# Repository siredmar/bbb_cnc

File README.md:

bbb_cnc
=======

Beaglebone Black Cape for CNC machines

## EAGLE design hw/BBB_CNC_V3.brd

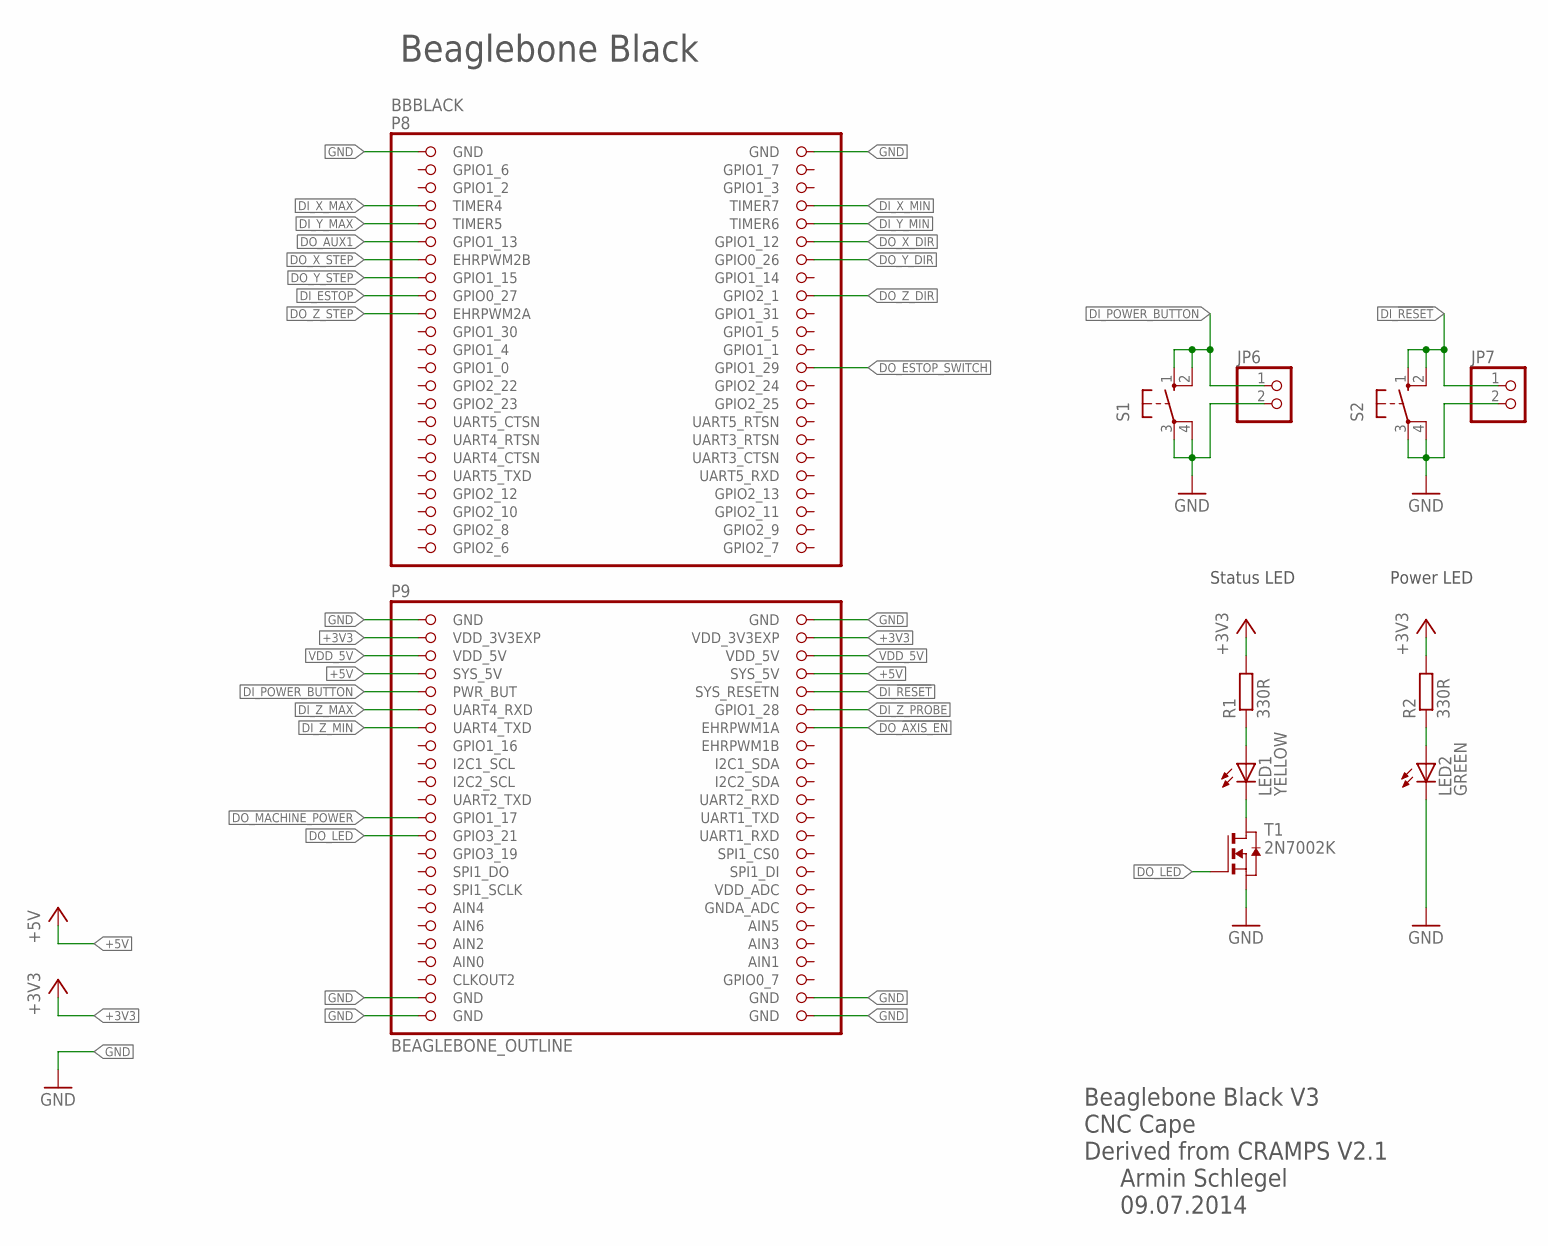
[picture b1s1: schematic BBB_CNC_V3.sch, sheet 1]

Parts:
BBBLACK: BEAGLEBONE_OUTLINE; BEAGLEBONE_SHIELD
JP6, JP7: PINHD-1X2; 1X02
LED1: YELLOW; SML0805
LED2: GREEN; SML0805
R1, R2: 330R; R0603
S1, S2: 10-XX; B3F-10XX
T1: 2N7002K; SOT-23

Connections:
+3V3: BBBLACK.49 (VDD_3V3EXP), BBBLACK.50 (VDD_3V3EXP), R1.2, R2.2; also elsewhere on the board
+5V: BBBLACK.53 (SYS_5V), BBBLACK.54 (SYS_5V); also elsewhere on the board
AIN0: BBBLACK.85 (AIN0)
DI_!RESET: BBBLACK.56 (SYS_RESETN), JP7.1, S2.1 (S), S2.2 (S1)
DI_ESTOP: BBBLACK.17 (GPIO0_27); also elsewhere on the board
DI_POWER_BUTTON: BBBLACK.55 (PWR_BUT), JP6.1, S1.1 (S), S1.2 (S1)
DI_X_MAX: BBBLACK.7 (TIMER4); also elsewhere on the board
DI_X_MIN: BBBLACK.8 (TIMER7); also elsewhere on the board
DI_Y_MAX: BBBLACK.9 (TIMER5); also elsewhere on the board
DI_Y_MIN: BBBLACK.10 (TIMER6); also elsewhere on the board
DI_Z_MAX: BBBLACK.57 (UART4_RXD); also elsewhere on the board
DI_Z_MIN: BBBLACK.59 (UART4_TXD); also elsewhere on the board
DI_Z_PROBE: BBBLACK.58 (GPIO1_28); also elsewhere on the board
DO_!AXIS_EN: BBBLACK.60 (EHRPWM1A); also elsewhere on the board
DO_AUX1: BBBLACK.11 (GPIO1_13); also elsewhere on the board
DO_ESTOP_SWITCH: BBBLACK.26 (GPIO1_29); also elsewhere on the board
DO_LED: BBBLACK.71 (GPIO3_21), T1.3 (G)
DO_MACHINE_POWER: BBBLACK.69 (GPIO1_17); also elsewhere on the board
DO_X_DIR: BBBLACK.12 (GPIO1_12); also elsewhere on the board
DO_X_STEP: BBBLACK.13 (EHRPWM2B); also elsewhere on the board
DO_Y_DIR: BBBLACK.14 (GPIO0_26); also elsewhere on the board
DO_Y_STEP: BBBLACK.15 (GPIO1_15); also elsewhere on the board
DO_Z_DIR: BBBLACK.18 (GPIO2_1); also elsewhere on the board
DO_Z_STEP: BBBLACK.19 (EHRPWM2A); also elsewhere on the board
GND: BBBLACK.1 (GND), BBBLACK.2 (GND), BBBLACK.47 (GND), BBBLACK.48 (GND), BBBLACK.89 (GND), BBBLACK.90 (GND), BBBLACK.91 (GND), BBBLACK.92 (GND), JP6.2, JP7.2, LED2.C, S1.3, S1.4 (P1), S2.3, S2.4 (P1), T1.2 (S); also elsewhere on the board
unnamed: LED1.C, T1.1 (D)
unnamed: LED1.A, R1.1
unnamed: LED2.A, R2.1
VDD_5V: BBBLACK.51 (VDD_5V), BBBLACK.52 (VDD_5V)

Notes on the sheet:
Status LED
Power LED
Beaglebone Black
Beaglebone Black V3 CNC Cape Derived from CRAMPS V2.1
Armin Schlegel 09.07.2014

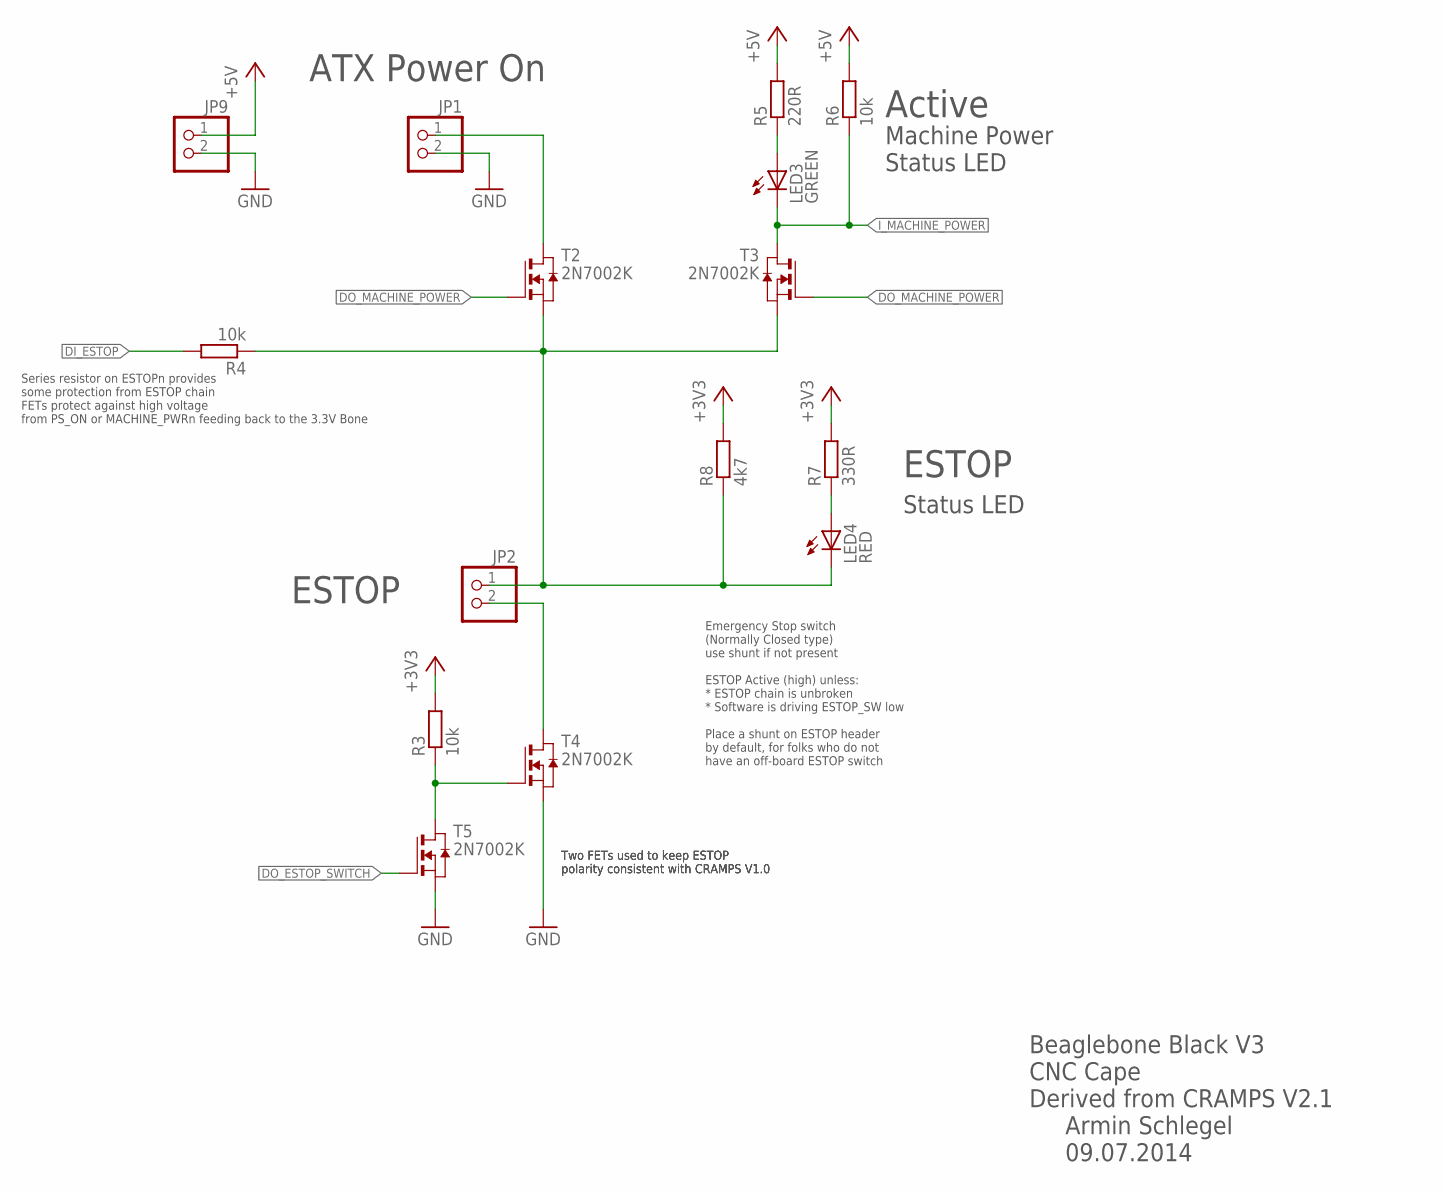
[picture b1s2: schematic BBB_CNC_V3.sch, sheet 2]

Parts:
JP1, JP2, JP9: PINHD-1X2; 1X02
LED3: GREEN; SML0805
LED4: RED; SML0805
R3, R4, R6: 10k; R0603
R5: 220R; R0603
R7: 330R; R0603
R8: 4k7; R0603
T2, T3, T4, T5: 2N7002K; SOT-23

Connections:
+3V3: R3.2, R7.2, R8.2; also elsewhere on the board
+5V: JP9.1, R5.2, R6.2; also elsewhere on the board
DI_ESTOP: R4.2; also elsewhere on the board
DO_ESTOP_SWITCH: T5.3 (G); also elsewhere on the board
DO_MACHINE_POWER: T2.3 (G), T3.3 (G); also elsewhere on the board
GND: JP1.2, JP9.2, T4.2 (S), T5.2 (S); also elsewhere on the board
I_MACHINE_POWER: LED3.C, R6.1, T3.1 (D); also elsewhere on the board
I_MACHINE_POWER1: JP2.1, LED4.C, R4.1, R8.1, T2.2 (S), T3.2 (S)
unnamed: JP1.1, T2.1 (D)
unnamed: R3.1, T4.3 (G), T5.1 (D)
unnamed: JP2.2, T4.1 (D)
unnamed: LED3.A, R5.1
unnamed: LED4.A, R7.1

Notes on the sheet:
Series resistor on ESTOPn provides some protection from ESTOP chain FETs protect against high voltage from PS_ON or MACHINE_PWRn feeding back to the 3.3V Bone
ATX Power On
Active
Two FETs used to keep ESTOP polarity consistent with CRAMPS V1.0
Emergency Stop switch (Normally Closed type) use shunt if not present
ESTOP Active (high) unless: * ESTOP chain is unbroken * Software is driving ESTOP_SW low
Place a shunt on ESTOP header by default, for folks who do not have an off-board ESTOP switch
ESTOP
Status LED
Machine Power Status LED
Beaglebone Black V3 CNC Cape Derived from CRAMPS V2.1
Armin Schlegel 09.07.2014

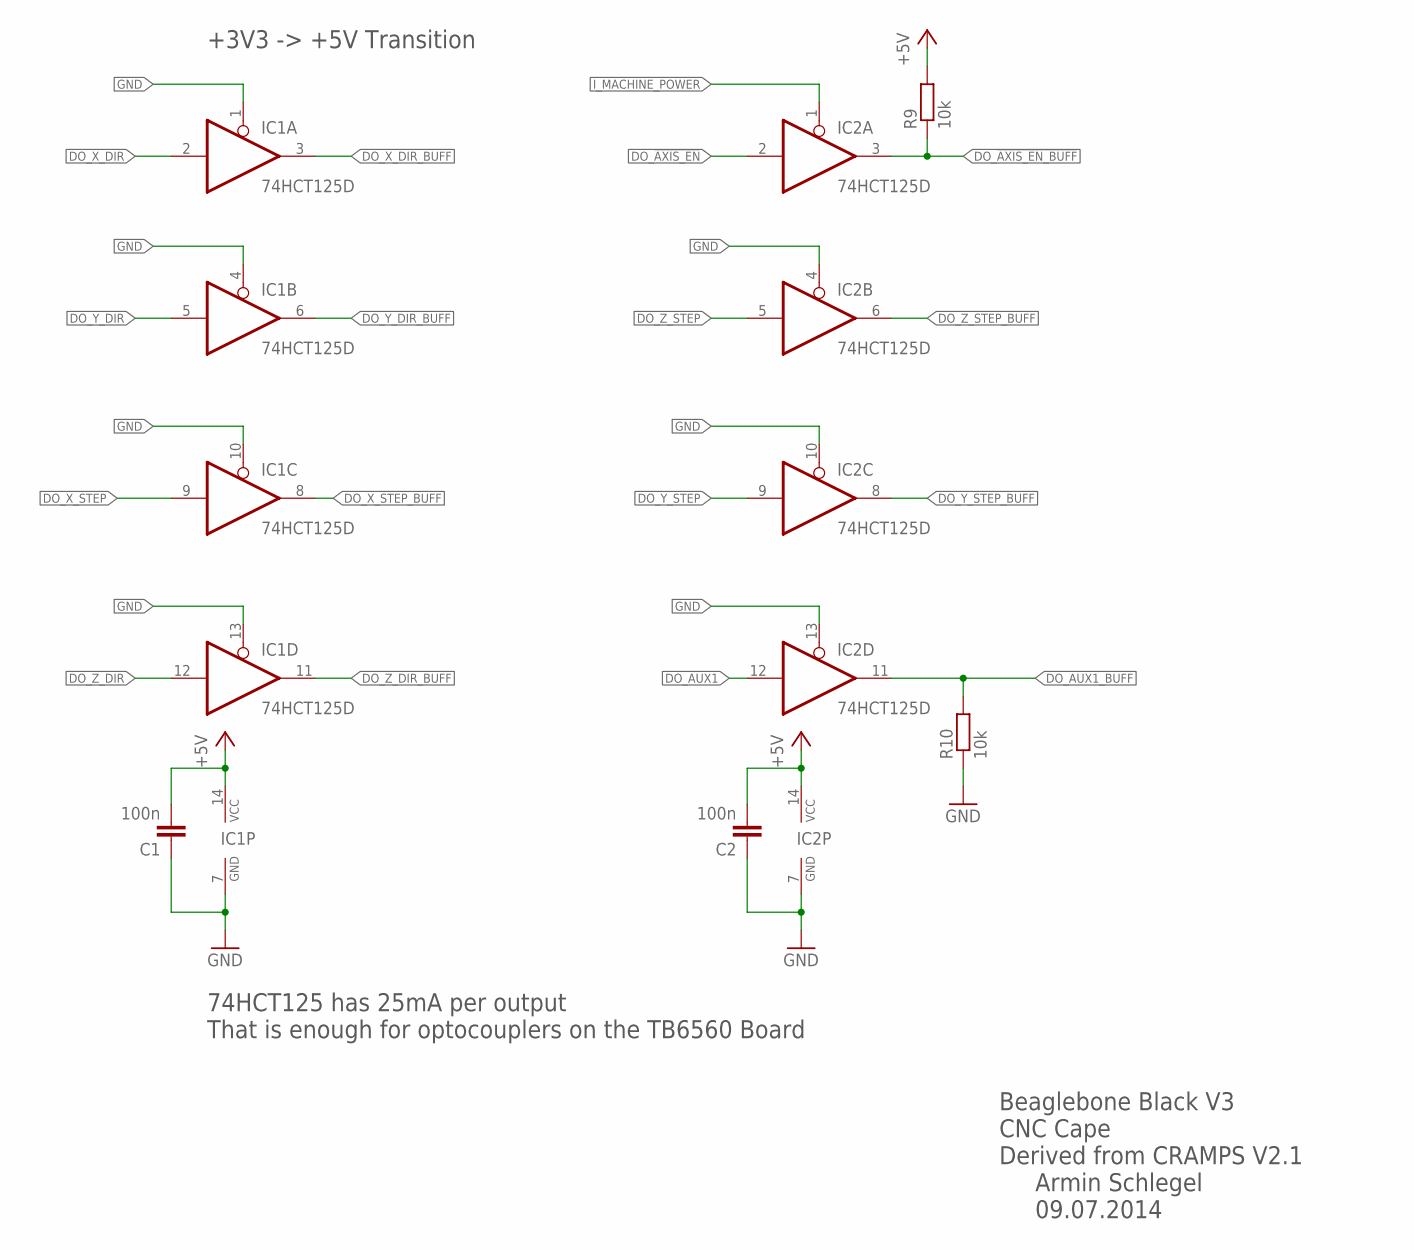
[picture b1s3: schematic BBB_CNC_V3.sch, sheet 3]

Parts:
C1, C2: 100n; C0603K
IC1, IC2: 74HCT125D; SO14
R9, R10: 10k; R0603

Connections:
+5V: C1.2, C2.2, IC1.14 (VCC), IC2.14 (VCC), R9.2; also elsewhere on the board
DO_!AXIS_EN: IC2.2 (I); also elsewhere on the board
DO_!AXIS_EN_BUFF: IC2.3 (O), R9.1; also elsewhere on the board
DO_AUX1: IC2.12 (I); also elsewhere on the board
DO_AUX1_BUFF: IC2.11 (O), R10.2; also elsewhere on the board
DO_X_DIR: IC1.2 (I); also elsewhere on the board
DO_X_DIR_BUFF: IC1.3 (O); also elsewhere on the board
DO_X_STEP: IC1.9 (I); also elsewhere on the board
DO_X_STEP_BUFF: IC1.8 (O); also elsewhere on the board
DO_Y_DIR: IC1.5 (I); also elsewhere on the board
DO_Y_DIR_BUFF: IC1.6 (O); also elsewhere on the board
DO_Y_STEP: IC2.9 (I); also elsewhere on the board
DO_Y_STEP_BUFF: IC2.8 (O); also elsewhere on the board
DO_Z_DIR: IC1.12 (I); also elsewhere on the board
DO_Z_DIR_BUFF: IC1.11 (O); also elsewhere on the board
DO_Z_STEP: IC2.5 (I); also elsewhere on the board
DO_Z_STEP_BUFF: IC2.6 (O); also elsewhere on the board
GND: C1.1, C2.1, IC1.1 (OE), IC1.4 (OE), IC1.7 (GND), IC1.10 (OE), IC1.13 (OE), IC2.4 (OE), IC2.7 (GND), IC2.10 (OE), IC2.13 (OE), R10.1; also elsewhere on the board
I_MACHINE_POWER: IC2.1 (OE); also elsewhere on the board

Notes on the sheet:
+3V3 -> +5V Transition
74HCT125 has 25mA per output That is enough for optocouplers on the TB6560 Board
Beaglebone Black V3 CNC Cape Derived from CRAMPS V2.1
Armin Schlegel 09.07.2014

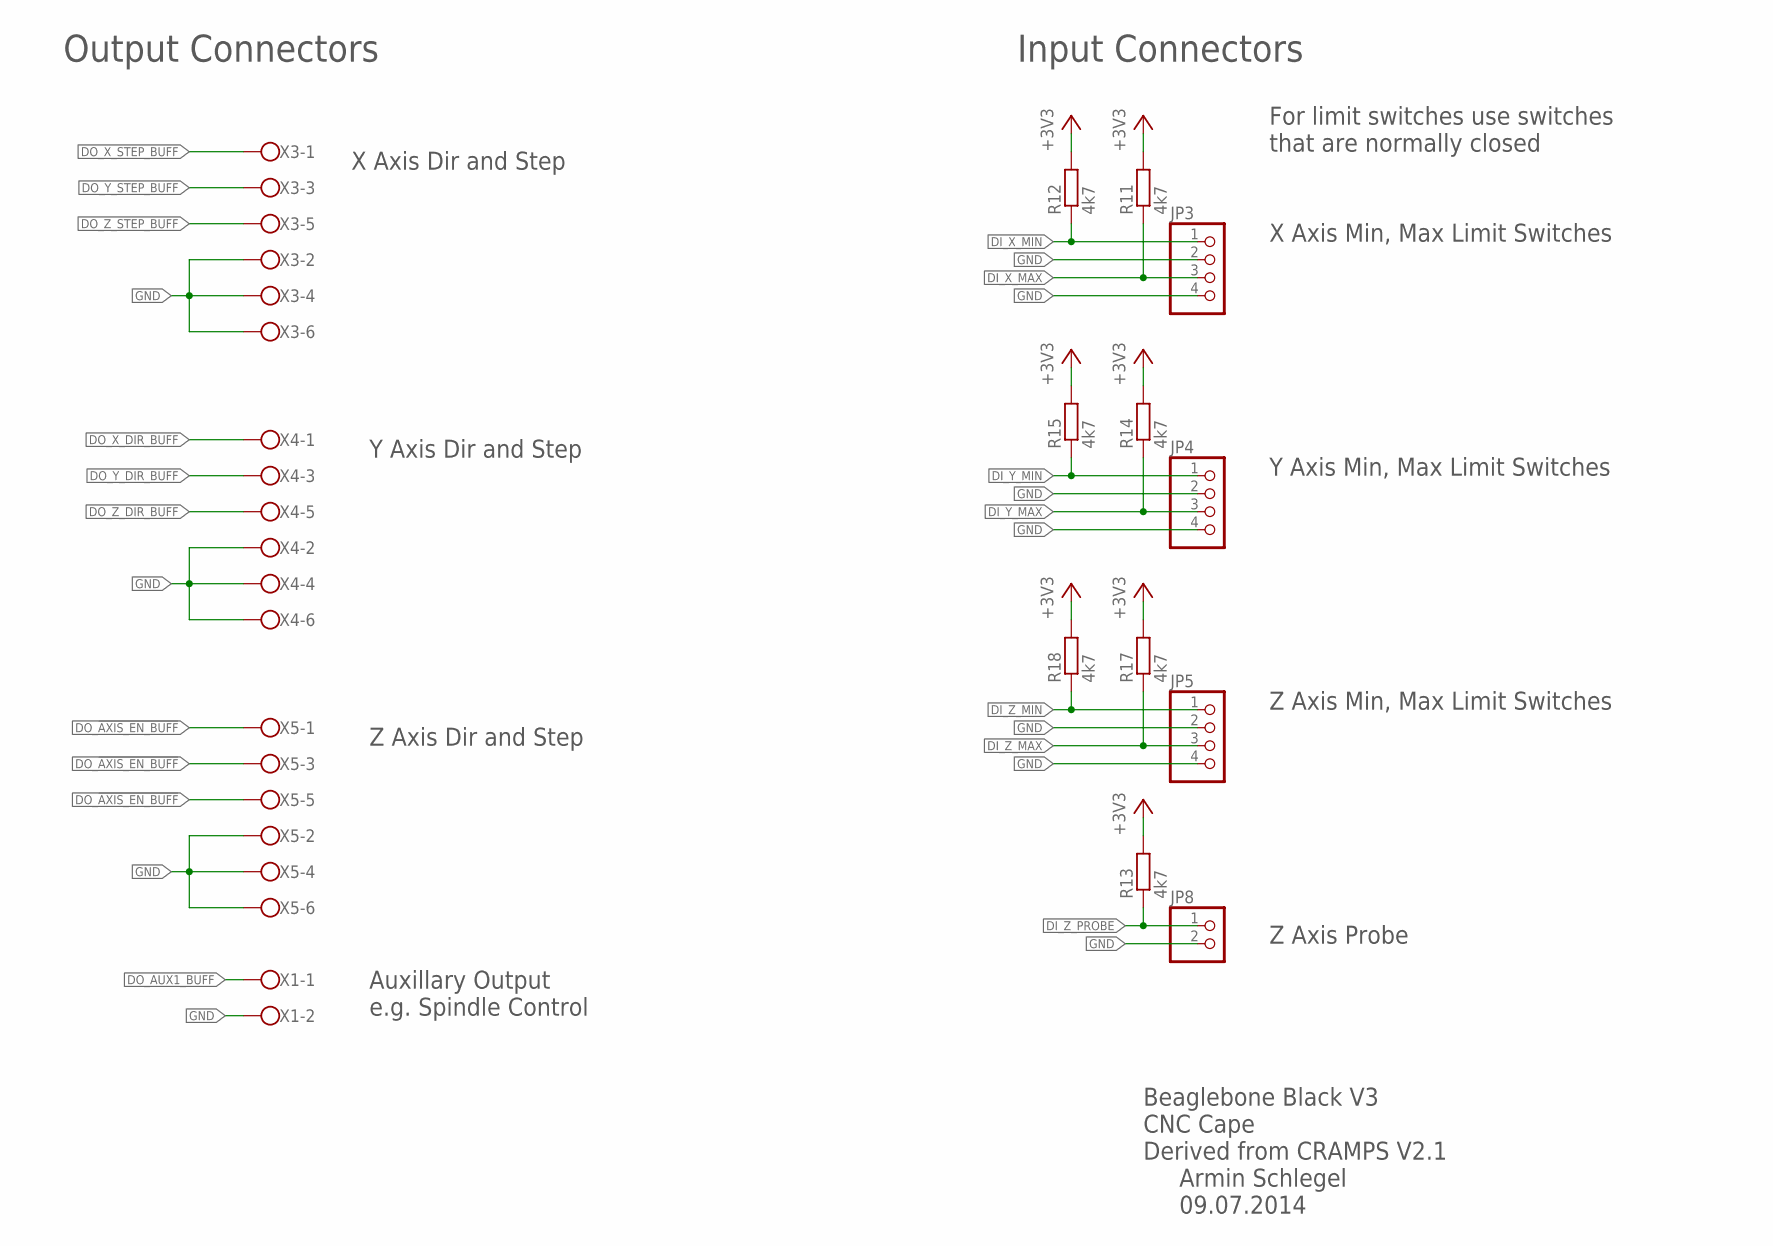
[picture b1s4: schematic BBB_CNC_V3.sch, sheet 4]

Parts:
JP3, JP4, JP5: PINHD-1X4; 1X04
JP8: PINHD-1X2; 1X02
R11, R12, R13, R14, R15, R17, R18: 4k7; R0603
X1: W237-102
X3, X4, X5: W237-136

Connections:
+3V3: R11.2, R12.2, R13.2, R14.2, R15.2, R17.2, R18.2; also elsewhere on the board
DI_X_MAX: JP3.3, R11.1; also elsewhere on the board
DI_X_MIN: JP3.1, R12.1; also elsewhere on the board
DI_Y_MAX: JP4.3, R14.1; also elsewhere on the board
DI_Y_MIN: JP4.1, R15.1; also elsewhere on the board
DI_Z_MAX: JP5.3, R17.1; also elsewhere on the board
DI_Z_MIN: JP5.1, R18.1; also elsewhere on the board
DI_Z_PROBE: JP8.1, R13.1; also elsewhere on the board
DO_!AXIS_EN_BUFF: X5.1, X5.3, X5.5; also elsewhere on the board
DO_AUX1_BUFF: X1.1; also elsewhere on the board
DO_X_DIR_BUFF: X4.1; also elsewhere on the board
DO_X_STEP_BUFF: X3.1; also elsewhere on the board
DO_Y_DIR_BUFF: X4.3; also elsewhere on the board
DO_Y_STEP_BUFF: X3.3; also elsewhere on the board
DO_Z_DIR_BUFF: X4.5; also elsewhere on the board
DO_Z_STEP_BUFF: X3.5; also elsewhere on the board
GND: JP3.2, JP3.4, JP4.2, JP4.4, JP5.2, JP5.4, JP8.2, X1.2, X3.2, X3.4, X3.6, X4.2, X4.4, X4.6, X5.2, X5.4, X5.6; also elsewhere on the board

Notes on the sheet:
Output Connectors
Input Connectors
X Axis Dir and Step
Y Axis Dir and Step
Z Axis Dir and Step
Z Axis Probe
X Axis Min, Max Limit Switches
Y Axis Min, Max Limit Switches
Z Axis Min, Max Limit Switches
Auxillary Output e.g. Spindle Control
For limit switches use switches that are normally closed
Beaglebone Black V3 CNC Cape Derived from CRAMPS V2.1
Armin Schlegel 09.07.2014

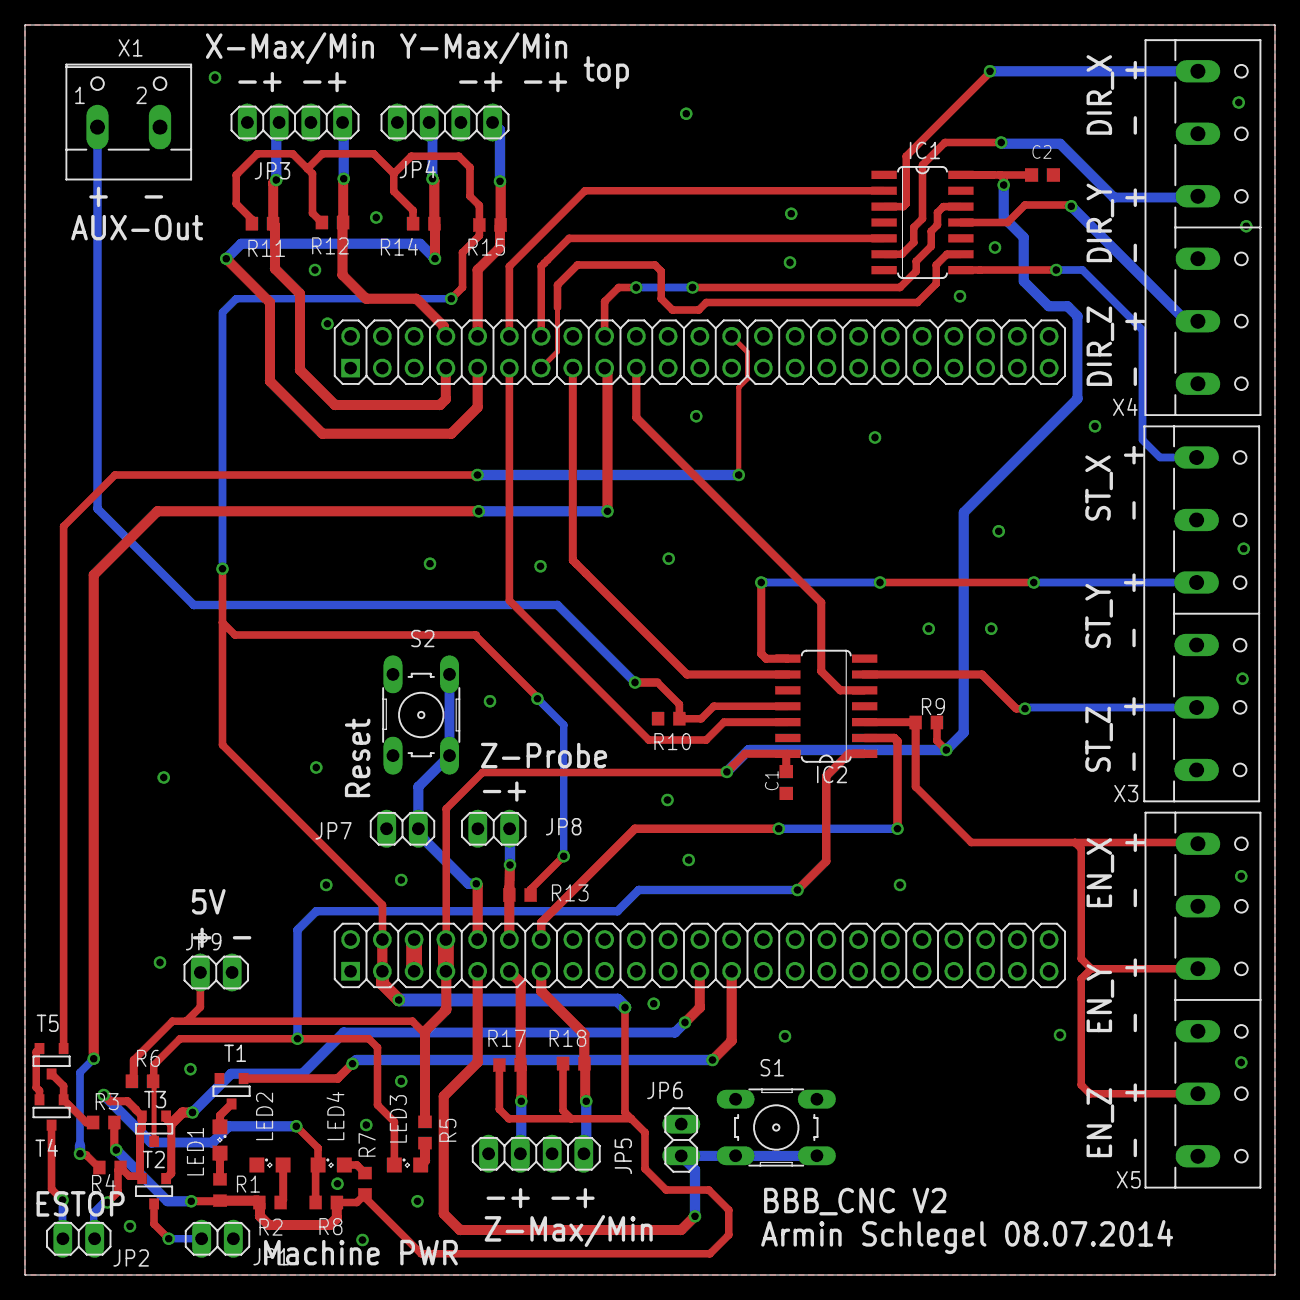
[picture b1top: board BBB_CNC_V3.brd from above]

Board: 2 copper layers, 100.0 x 100.0 mm, 46 parts (0 on the bottom side), 43 nets.

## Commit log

2014-07-03 repo initialized
2014-07-04 version 1 of schematic finished
2014-07-04 deleted backup files
2014-07-06 modified v1, finished pcb
2014-07-08 V2, gerber files for Itead
2014-07-08 added Itead dru and cam files
2014-07-08 added zip for itead containing gerber file
2014-07-09 corrected error on v2 -> v3
2014-07-09 updated gerber files to V3
2014-07-30 received pcbs from itead
